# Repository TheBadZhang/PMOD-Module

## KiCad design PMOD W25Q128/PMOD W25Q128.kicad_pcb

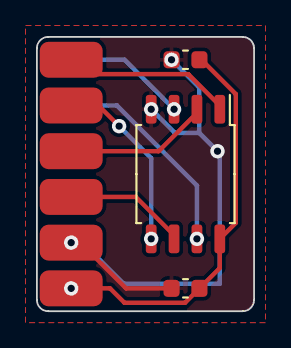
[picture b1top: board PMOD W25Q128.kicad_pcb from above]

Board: 2 copper layers, 12.1 x 15.2 mm, 4 parts (0 on the bottom side), 8 nets.

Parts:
C1, C2: 0.1uF; C_0603_1608Metric
J1: Conn_02x06_Top_Bottom; PMOD_Peripheral_type_2
U1: W25Q128JVS; SOIC-8_5.23x5.23mm_P1.27mm

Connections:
/PMOD-SPI/CS: J1.1, U1.1 (~CS)
/PMOD-SPI/GND: C1.2, C2.2, J1.5, J1.11, U1.4 (GND)
/PMOD-SPI/INT: J1.7, U1.3 (IO2)
/PMOD-SPI/MISO: J1.3, U1.2 (DO(IO1))
/PMOD-SPI/MOSI: J1.2, U1.5 (DI(IO0))
/PMOD-SPI/RST: J1.8, U1.7 (IO3)
/PMOD-SPI/SCK: J1.4, U1.6 (CLK)
/PMOD-SPI/VCC: C1.1, C2.1, J1.6, J1.12, U1.8 (VCC)

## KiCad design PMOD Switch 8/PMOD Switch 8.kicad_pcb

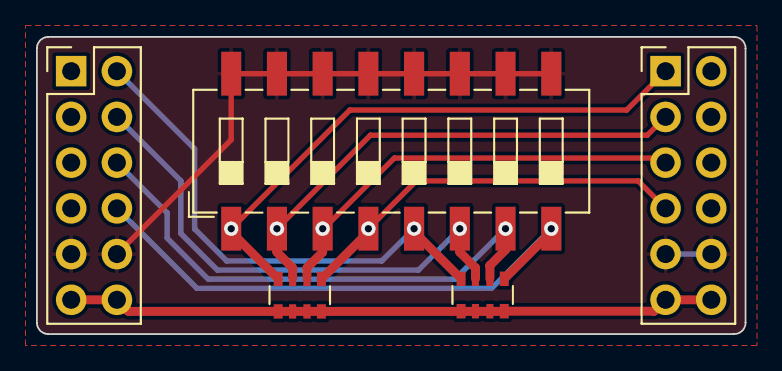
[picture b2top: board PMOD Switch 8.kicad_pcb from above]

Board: 4 copper layers, 39.4 x 16.5 mm, 5 parts (0 on the bottom side), 10 nets.

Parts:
J1, J2: Conn_02x06_Top_Bottom; PMOD-HOST
RN1, RN2: 5.1K; R_Array_Convex_4x0603
SW1: SW_DIP_x08; SW_DIP_SPSTx08_Slide_6.7x21.88mm_W8.61mm_P2.54mm_LowProfile

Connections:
/PMOD GPIO/GND: J1.5, J1.11, J2.5, J2.11, SW1.9, SW1.10, SW1.11, SW1.12, SW1.13, SW1.14, SW1.15, SW1.16
/PMOD GPIO/IO1: J1.1, J2.1, RN1.8 (R1.2), SW1.1
/PMOD GPIO/IO2: J1.2, J2.2, RN1.7 (R2.2), SW1.2
/PMOD GPIO/IO3: J1.3, J2.3, RN1.6 (R3.2), SW1.3
/PMOD GPIO/IO4: J1.4, J2.4, RN1.5 (R4.2), SW1.4
/PMOD GPIO/IO5: J1.7, J2.7, RN2.8 (R1.2), SW1.5
/PMOD GPIO/IO6: J1.8, J2.8, RN2.7 (R2.2), SW1.6
/PMOD GPIO/IO7: J1.9, J2.9, RN2.6 (R3.2), SW1.7
/PMOD GPIO/IO8: J1.10, J2.10, RN2.5 (R4.2), SW1.8
/PMOD GPIO/VCC: J1.6, J1.12, J2.6, J2.12, RN1.1 (R1.1), RN1.2 (R2.1), RN1.3 (R3.1), RN1.4 (R4.1), RN2.1 (R1.1), RN2.2 (R2.1), RN2.3 (R3.1), RN2.4 (R4.1)

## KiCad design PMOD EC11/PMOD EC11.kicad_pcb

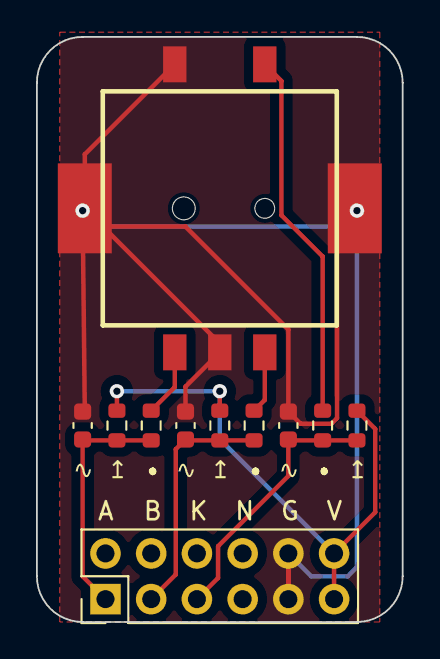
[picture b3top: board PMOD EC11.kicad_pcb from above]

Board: 2 copper layers, 20.3 x 32.5 mm, 11 parts (0 on the bottom side), 8 nets.

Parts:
C1, C2, C3: 10nF; C_0603_1608Metric
J2: Conn_02x06_Top_Bottom; PMOD-HOST
R1, R2: 10K; R_0603_1608Metric
R3, R4, R5: 470R; R_0603_1608Metric
R6: 4.7K; R_0603_1608Metric
U1: EC11_TP

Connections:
+3V3: J2.6, J2.12, R1.1, R2.1, R6.1
/EC11/EC11_A: C1.1, J2.1, R1.2, R3.1
/EC11/EC11_B: C2.1, J2.2, R2.2, R4.1
/EC11/EC11_KEY: C3.1, J2.3, R5.2, R6.2
GND: C1.2, C2.2, C3.2, J2.5, J2.11, U1.C, U1.D, U1.S
unnamed: R3.2, U1.A
unnamed: R4.2, U1.B
unnamed: R5.1, U1.E

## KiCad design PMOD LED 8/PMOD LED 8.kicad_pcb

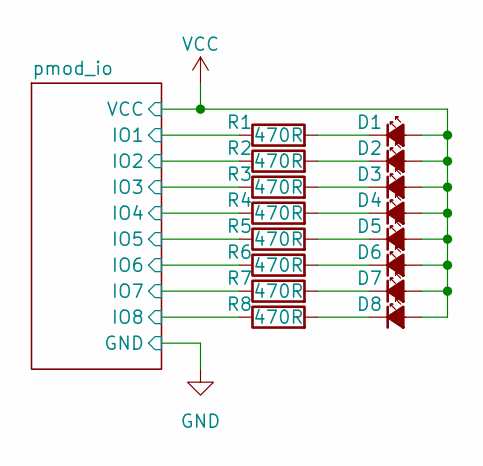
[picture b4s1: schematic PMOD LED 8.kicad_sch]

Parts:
D1, D2, D3, D4, D5, D6, D7, D8: LED_Small_Filled; LED_0603_1608Metric
R1, R2, R3, R4, R5, R6, R7, R8: 470R; R_0603_1608Metric

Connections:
/pmod_io/IO1: R1.1; also elsewhere on the board
/pmod_io/IO2: R2.1; also elsewhere on the board
/pmod_io/IO3: R3.1; also elsewhere on the board
/pmod_io/IO4: R4.1; also elsewhere on the board
/pmod_io/IO5: R5.1; also elsewhere on the board
/pmod_io/IO6: R6.1; also elsewhere on the board
/pmod_io/IO7: R7.1; also elsewhere on the board
/pmod_io/IO8: R8.1; also elsewhere on the board
unnamed: D1.1 (K), R1.2
unnamed: D2.1 (K), R2.2
unnamed: D3.1 (K), R3.2
unnamed: D4.1 (K), R4.2
unnamed: D5.1 (K), R5.2
unnamed: D6.1 (K), R6.2
unnamed: D7.1 (K), R7.2
unnamed: D8.1 (K), R8.2
VCC: D1.2 (A), D2.2 (A), D3.2 (A), D4.2 (A), D5.2 (A), D6.2 (A), D7.2 (A), D8.2 (A); also elsewhere on the board

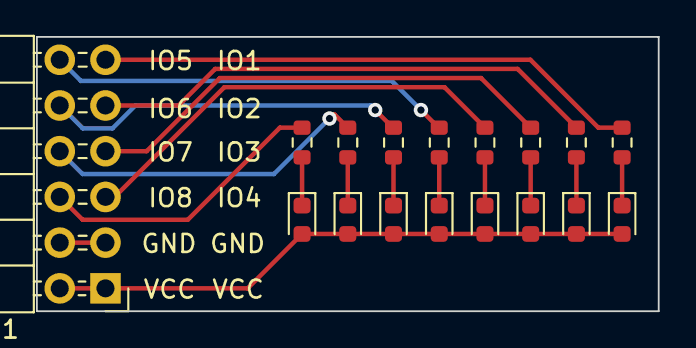
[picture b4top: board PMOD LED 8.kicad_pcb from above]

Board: 2 copper layers, 34.5 x 15.2 mm, 17 parts (0 on the bottom side), 18 nets.

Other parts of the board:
J1: Conn_02x06_Odd_Even; PinHeader_2x06_P2.54mm_Horizontal

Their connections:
/pmod_io/IO1: J1.11; also elsewhere on the board
/pmod_io/IO2: J1.9; also elsewhere on the board
/pmod_io/IO3: J1.7; also elsewhere on the board
/pmod_io/IO4: J1.5; also elsewhere on the board
/pmod_io/IO5: J1.12; also elsewhere on the board
/pmod_io/IO6: J1.10; also elsewhere on the board
/pmod_io/IO7: J1.8; also elsewhere on the board
/pmod_io/IO8: J1.6; also elsewhere on the board
GND: J1.3, J1.4
VCC: J1.1, J1.2; also elsewhere on the board

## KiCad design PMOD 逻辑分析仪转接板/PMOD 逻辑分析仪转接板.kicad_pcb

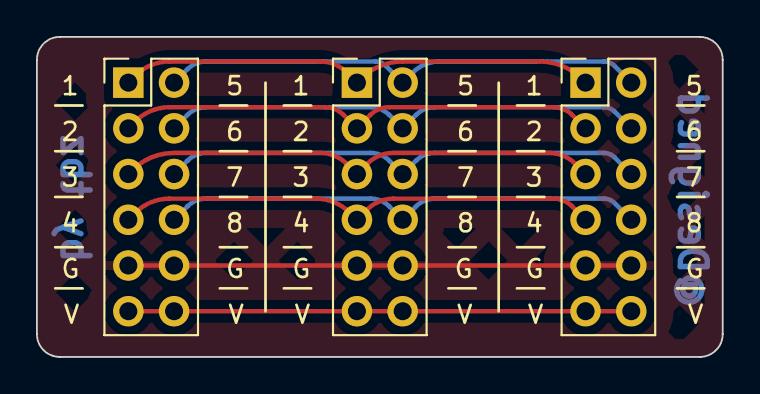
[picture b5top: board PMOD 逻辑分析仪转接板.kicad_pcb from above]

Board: 2 copper layers, 38.1 x 17.8 mm, 3 parts (0 on the bottom side), 10 nets.

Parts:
J1, J2, J3: Conn_02x06_Top_Bottom; PMOD-HOST

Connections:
/gpio_debug/GND: J1.5, J1.11, J2.5, J2.11, J3.5, J3.11
/gpio_debug/IO1: J1.1, J2.1, J3.1
/gpio_debug/IO2: J1.2, J2.2, J3.2
/gpio_debug/IO3: J1.3, J2.3, J3.3
/gpio_debug/IO4: J1.4, J2.4, J3.4
/gpio_debug/IO5: J1.7, J2.7, J3.7
/gpio_debug/IO6: J1.8, J2.8, J3.8
/gpio_debug/IO7: J1.9, J2.9, J3.9
/gpio_debug/IO8: J1.10, J2.10, J3.10
/gpio_debug/VCC: J1.6, J1.12, J2.6, J2.12, J3.6, J3.12

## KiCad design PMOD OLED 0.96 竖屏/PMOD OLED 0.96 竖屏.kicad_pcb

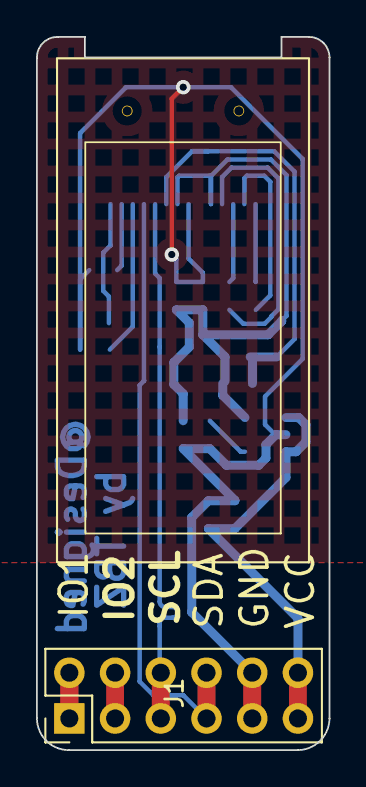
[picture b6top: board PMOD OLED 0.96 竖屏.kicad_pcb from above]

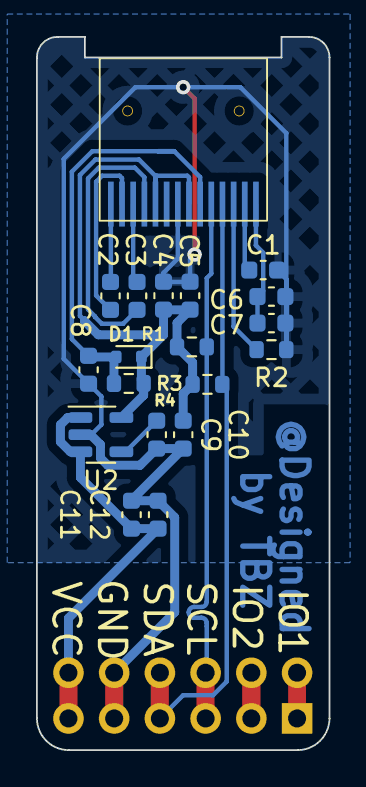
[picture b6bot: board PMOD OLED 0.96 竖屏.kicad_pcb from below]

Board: 2 copper layers, 16.3 x 39.6 mm, 20 parts (18 on the bottom side), 16 nets.

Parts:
C1: 2.2uF; C_0603_1608Metric
C2, C3: 1uF; C_0603_1608Metric
C4, C6, C10, C11: 4.7uF; C_0603_1608Metric
C5, C7, C12: 0.1uF; C_0603_1608Metric
C8: 10uF; C_0603_1608Metric
C9: 22nF; C_0603_1608Metric
D1: 1N4148WT; D_SOD-523
J1: Conn_02x06_Top_Bottom; PMOD-Peripheral
R1, R3, R4: 4.7K; R_0603_1608Metric
R2: 560K; R_0603_1608Metric
U1: iic_oled_12864_ssd1312
U2: RT9193-33GB; SOT-23-5

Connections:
+3V3: C4.1, C5.1, C10.2, D1.1 (K), R1.1, R3.1, R4.1, U1.5 (VBAT), U1.8 (VDD), U2.5 (Vout)
/PMOD IIC/IO1: J1.1, J1.7
/PMOD IIC/IO2: J1.2, J1.8
/PMOD IIC/VCC: C11.1, C12.1, J1.6, J1.12, U2.1 (Vin), U2.3 (EN)
/SCL: J1.3, J1.9, R1.2, U1.10 (SCL)
/SDA: J1.4, J1.10, R3.2, U1.11 (SDA)
GND: C1.2, C4.2, C5.2, C6.2, C7.2, C8.2, C9.2, C10.1, C11.2, C12.2, J1.5, J1.11, R2.1, U1.7 (VSS), U2.2 (GND)
unnamed: C8.1, D1.2 (A), R4.2, U1.9 (RES#)
unnamed: C3.1, U1.4 (C1N)
unnamed: C3.2, U1.3 (C1P)
unnamed: C2.1, U1.2 (C2N)
unnamed: C2.2, U1.1 (C2P)
unnamed: R2.2, U1.12 (IREF)
unnamed: C6.1, C7.1, U1.14 (VCC)
unnamed: C1.1, U1.13 (VCOMH)
unnamed: C9.1, U2.4 (BP)

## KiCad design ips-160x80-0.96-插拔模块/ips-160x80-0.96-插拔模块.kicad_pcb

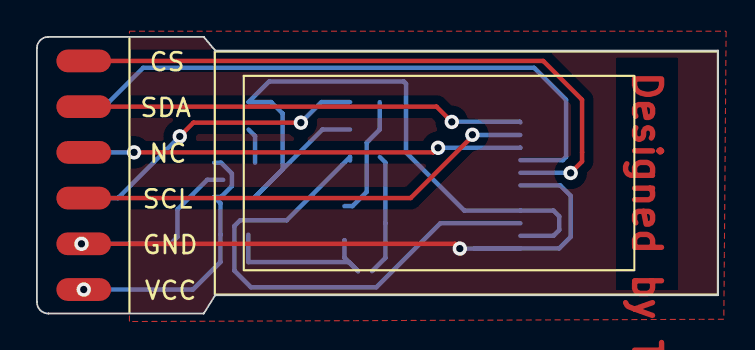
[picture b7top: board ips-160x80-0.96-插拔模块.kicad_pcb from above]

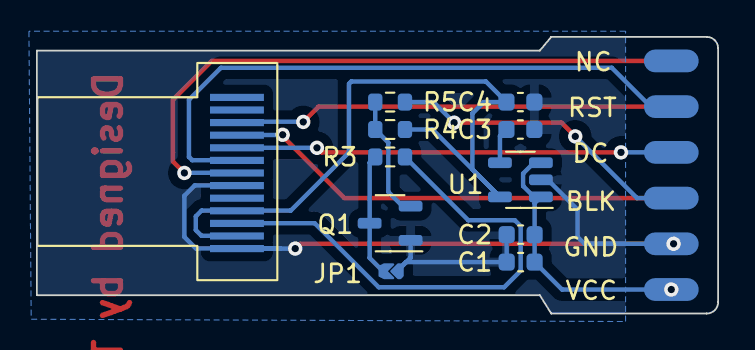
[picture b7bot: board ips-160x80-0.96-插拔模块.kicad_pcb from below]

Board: 2 copper layers, 37.8 x 15.4 mm, 12 parts (10 on the bottom side), 13 nets.

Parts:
C1, C4: 4.7uF; C_0603_1608Metric
C2: 104; C_0603_1608Metric
C3: 22nF; C_0603_1608Metric
J1: Conn_02x06_Odd_Even; 双面贴片排针
JP1: SolderJumper_2_Open; Jumper-2-0402-Type_A
Q1: S8050; SOT-23-3
R3: 10R; R_0603_1608Metric
R4: 10K; R_0603_1608Metric
R5: 1K; R_0603_1608Metric
U1: RT9193-33GB; SOT-23-5
U4: ips_0.96_16080; ips-16080-0.96

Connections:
/3v3_ldo/GND: C1.2, C2.2, C3.2, C4.1, J1.9, J1.10, JP1.1 (A), Q1.1 (E), U1.2 (GND), U4.8 (GND), U4.13 (GND)
/3v3_ldo/VIN: C1.1, C2.1, J1.11, J1.12, U1.1 (Vin), U1.3 (EN)
/3v3_ldo/VOUT: C4.2, R4.1, U1.5 (Vout), U4.10 (VDD), U4.12 (LEDA)
/PMOD_SPI/CS: J1.1, U4.7 (CS)
/PMOD_SPI/IO7: J1.6, U4.5 (D/C)
/PMOD_SPI/IO8: J1.8, R5.1
/PMOD_SPI/MOSI: J1.3, U4.3 (SDA)
/PMOD_SPI/RST: J1.4, U4.6 (RESET)
/PMOD_SPI/SCK: J1.7, U4.4 (SCL)
unnamed: JP1.2 (B), Q1.3 (C), R3.1
unnamed: Q1.2 (B), R4.2, R5.2
unnamed: C3.1, U1.4 (BP)
unnamed: R3.2, U4.11 (LEDK)

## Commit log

2023-06-18 pmod-8leds 最简单基础的 pmod 模块
2023-06-18 只有文件夹备份才不会被提交
2023-06-18 这个也算是某种程度上的pmod了（虽然是贴片排针
2023-06-21 更新了ips模块的模型
2023-07-06 逻辑分析仪转接板和OLED模块
2023-07-06 修改了项目的命名
2023-08-19 编码器模块
2023-08-19 SHT40 温湿度传感器模块
2023-08-19 8位贴片开关 模块
2023-10-02 添加了新的PMOD 模块
